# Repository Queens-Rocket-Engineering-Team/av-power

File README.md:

# Avionics Power Delivery (Power Module, Backplane, Screw Switch, etc)
> 2023-2026 Season - Power Delivery Projects

-  Repo contains board's **firmware**, **schematics**, and related **documentation and datasheets**.
-  The **Main** branch contains current functional hardware/software
-  **Branches** contain board revisions/versions or planned features/fixes.
-  If you're contributing, **make sure you're working in a branch other than Main**

### Folder Structure
- [`/Schematics`](./Schematics/) : PCB design files (KiCad V8)  
- [`/Firmware`](./Firmware/) : Arduino C/C++ code (for STM)
- [`/Datasheets`](./Datasheets/) : Datasheets and reference materials

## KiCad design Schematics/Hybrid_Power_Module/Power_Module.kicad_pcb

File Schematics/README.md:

# Schematics

This directory contains all schematics involved in this iteration of the Avionics Power Deliver system.

## Backplane
- Single, large PCB
- Connects all stack "modules" (PCBs)
- Allows communication between modules
- Cleaner routing for power

## Power Module
- Facilitates connections between backplane and external devices
	- Batteries
	- Screw switches

## Screw switches
- Supports manual enabling of power to avionics via screws
- Connected through Power Module

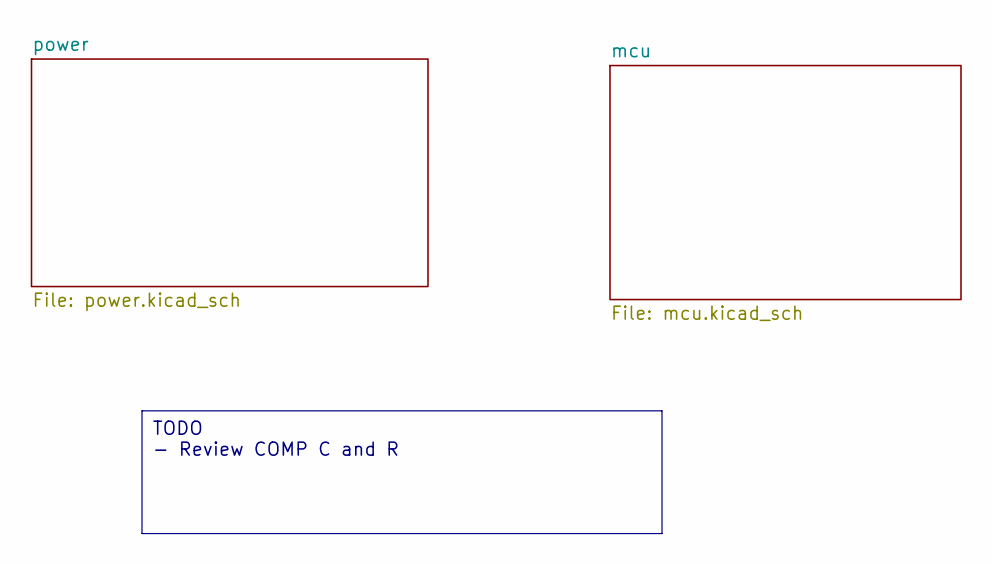
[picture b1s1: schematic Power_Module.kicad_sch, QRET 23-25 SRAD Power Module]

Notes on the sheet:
TODO - Review COMP C and R

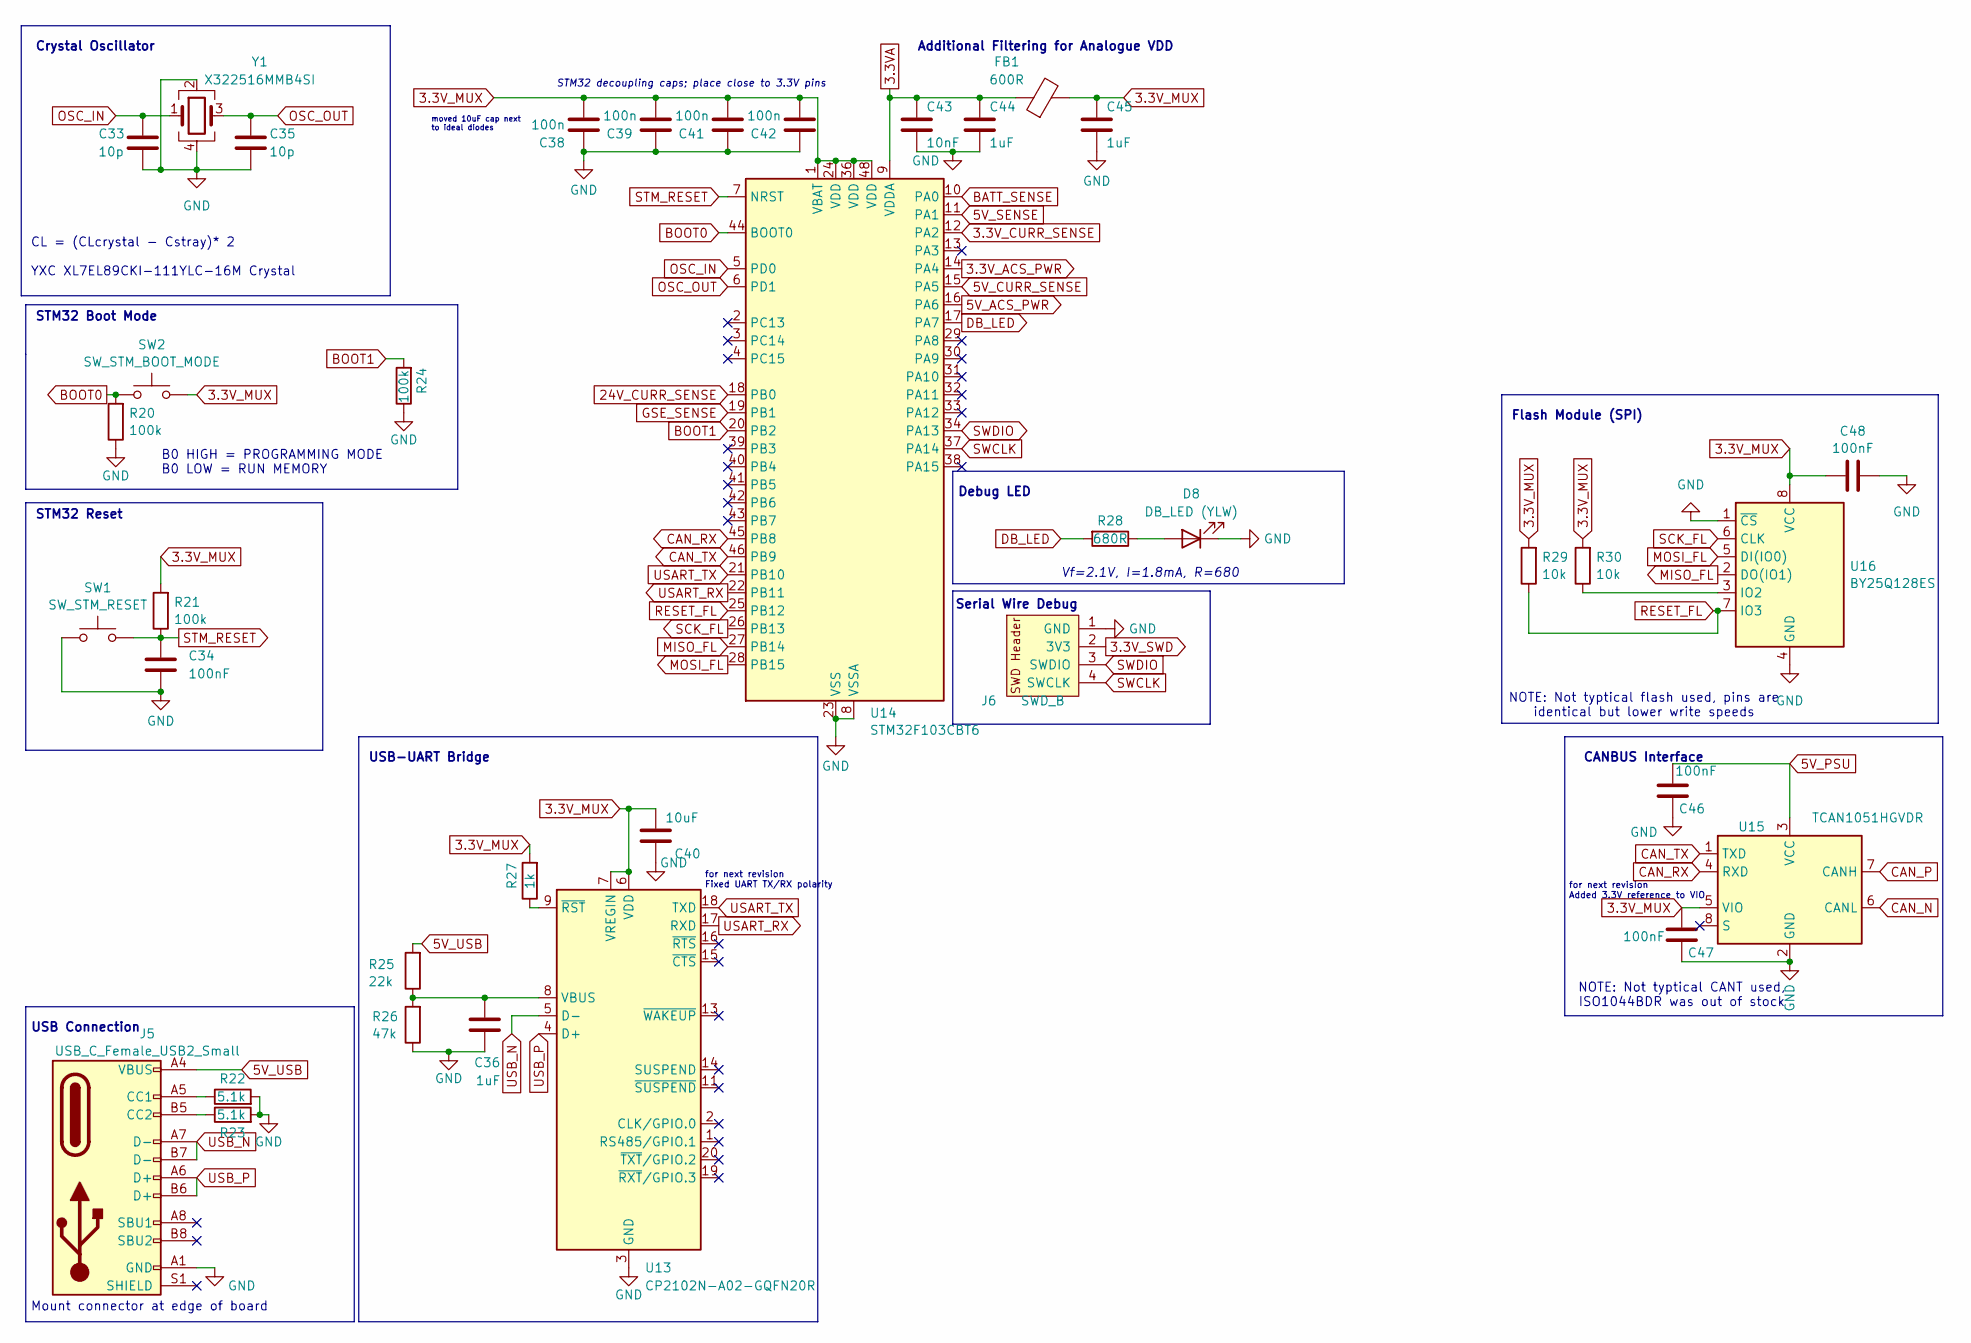
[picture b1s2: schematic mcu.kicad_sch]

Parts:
C33, C35: 10p; C_0402_1005Metric; LCSC C32949
C34, C46, C47, C48: 100nF; C_0603_1608Metric; LCSC C14663
C36, C44, C45: 1uF; C_0603_1608Metric; LCSC C15849
C38, C39, C41, C42: 100n; C_0402_1005Metric; LCSC C1525
C40: 10uF; C_0603_1608Metric; LCSC C96446
C43: 10nF; C_0603_1608Metric; LCSC C57112
D8: DB_LED (YLW); LED_0603_1608Metric; LCSC C2290
FB1: 600R; L_0603_1608Metric; LCSC C1002
J5: USB_C_Female_USB2_Small; USB_C_DB-108PWB; LCSC C5178541
J6: SWD_B; SWD_PinHeader_1x04_P2.54mm_Horizontal_SMD; Digikey 952-3233-ND
R20, R21, R24: 100k; R_0603_1608Metric; LCSC C25803
R22, R23: 5.1k; R_0603_1608Metric; LCSC C23186
R25: 22k; R_0603_1608Metric; LCSC C31850
R26: 47k; R_0603_1608Metric; LCSC C25819
R27: 1k; R_0603_1608Metric; LCSC C21190
R28: 680R; R_0603_1608Metric; LCSC C23228
R29, R30: 10k; R_0603_1608Metric; LCSC C25804
SW1: SW_STM_RESET; SW_Push_1P1T_XKB_TS-1187A; LCSC C318884
SW2: SW_STM_BOOT_MODE; SW_Push_1P1T_XKB_TS-1187A; LCSC C318884
U13: CP2102N-A02-GQFN20R; QFN-20-1EP_3x3mm; LCSC C969913
U14: STM32F103CBT6; LQFP-48_7x7mm_P0.5mm; LCSC C8304
U15: TCAN1051HGVDR; SOIC_1044BDR_TEX; Digikey 296-44225-1-ND
U16: BY25Q128ES; SOIC-8_5.23x5.23mm_P1.27mm; Digikey 5369-BY25Q128ESSIG(R)CT-ND
Y1: X322516MMB4SI; Crystal_SMD_3225-4Pin_3.2x2.5mm; LCSC C13738

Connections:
3.3VA: C43.1, C44.1, FB1.1, U14.9 (VDDA)
3.3V_ACS_PWR: U14.14 (PA4); also elsewhere on the board
3.3V_CURR_SENSE: U14.12 (PA2); also elsewhere on the board
3.3V_MUX: C38.2, C39.2, C40.1, C41.2, C42.2, C45.1, C47.1, C48.1, FB1.2, R21.2, R27.2, R29.2, R30.2, SW2.2, U13.6 (VDD), U13.7 (VREGIN), U14.1 (VBAT), U14.24 (VDD), U14.36 (VDD), U14.48 (VDD), U15.5 (VIO), U16.8 (VCC); also elsewhere on the board
3.3V_SWD: J6.2 (3V3); also elsewhere on the board
5V_ACS_PWR: U14.16 (PA6); also elsewhere on the board
5V_CURR_SENSE: U14.15 (PA5); also elsewhere on the board
5V_PSU: C46.1, U15.3 (VCC); also elsewhere on the board
5V_SENSE: U14.11 (PA1); also elsewhere on the board
5V_USB: J5.A4 (VBUS), J5.A9 (VBUS), J5.B4 (VBUS), J5.B9 (VBUS), R25.2; also elsewhere on the board
24V_CURR_SENSE: U14.18 (PB0); also elsewhere on the board
BATT_SENSE: U14.10 (PA0); also elsewhere on the board
BOOT0: R20.2, SW2.1, U14.44 (BOOT0)
BOOT1: R24.2, U14.20 (PB2)
CAN_N: U15.6 (CANL); also elsewhere on the board
CAN_P: U15.7 (CANH); also elsewhere on the board
CAN_RX: U14.45 (PB8), U15.4 (RXD)
CAN_TX: U14.46 (PB9), U15.1 (TXD)
DB_LED: R28.2, U14.17 (PA7)
GND: C33.2, C34.2, C35.2, C36.1, C38.1, C39.1, C40.2, C41.1, C42.1, C43.2, C44.2, C45.2, C46.2, C47.2, C48.2, D8.1 (K), J5.A1 (GND), J5.A12 (GND), J5.B1 (GND), J5.B12 (GND), J6.1 (GND), R20.1, R22.2, R23.2, R24.1, R26.1, SW1.1, U13.3 (GND), U13.12 (GND), U13.21 (GND), U14.8 (VSSA), U14.23 (VSS), U14.35 (VSS), U14.47 (VSS), U15.2 (GND), U16.1 (~CS), U16.4 (GND), Y1.2, Y1.4; also elsewhere on the board
GSE_SENSE: U14.19 (PB1); also elsewhere on the board
MISO_FL: U14.27 (PB14), U16.2 (DO(IO1))
MOSI_FL: U14.28 (PB15), U16.5 (DI(IO0))
unnamed: D8.2 (A), R28.1
unnamed: J5.A5 (CC1), R22.1
unnamed: J5.B5 (CC2), R23.1
unnamed: C36.2, R25.1, R26.2, U13.8 (VBUS)
unnamed: R27.1, U13.9 (~RST)
unnamed: R30.1, U16.3 (IO2)
OSC_IN: C33.1, U14.5 (PD0), Y1.1
OSC_OUT: C35.1, U14.6 (PD1), Y1.3
RESET_FL: R29.1, U14.25 (PB12), U16.7 (IO3)
SCK_FL: U14.26 (PB13), U16.6 (CLK)
STM_RESET: C34.1, R21.1, SW1.2, U14.7 (NRST)
SWCLK: J6.4 (SWCLK), U14.37 (PA14)
SWDIO: J6.3 (SWDIO), U14.34 (PA13)
USART_RX: U13.17 (RXD), U14.22 (PB11)
USART_TX: U13.18 (TXD), U14.21 (PB10)
USB_N: J5.A7 (D-), J5.B7 (D-), U13.5 (D-)
USB_P: J5.A6 (D+), J5.B6 (D+), U13.4 (D+)

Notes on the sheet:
STM32 Reset
STM32 decoupling caps; place close to 3.3V pins
NOTE: Not typtical CANT used, ISO1044BDR was out of stock
Vf=2.1V, I=1.8mA, R=680
CANBUS Interface
for next revision Fixed UART TX/RX polarity
Flash Module (SPI)
NOTE: Not typtical flash used, pins are identical but lower write speeds
Serial Wire Debug
Debug LED
B0 HIGH = PROGRAMMING MODE B0 LOW = RUN MEMORY
USB-UART Bridge
CL = (CLcrystal - Cstray)* 2 YXC XL7EL89CKI-111YLC-16M Crystal
Mount connector at edge of board
Crystal Oscillator
for next revision Added 3.3V reference to VIO
moved 10uF cap next to ideal diodes
STM32 Boot Mode
USB Connection
Additional Filtering for Analogue VDD

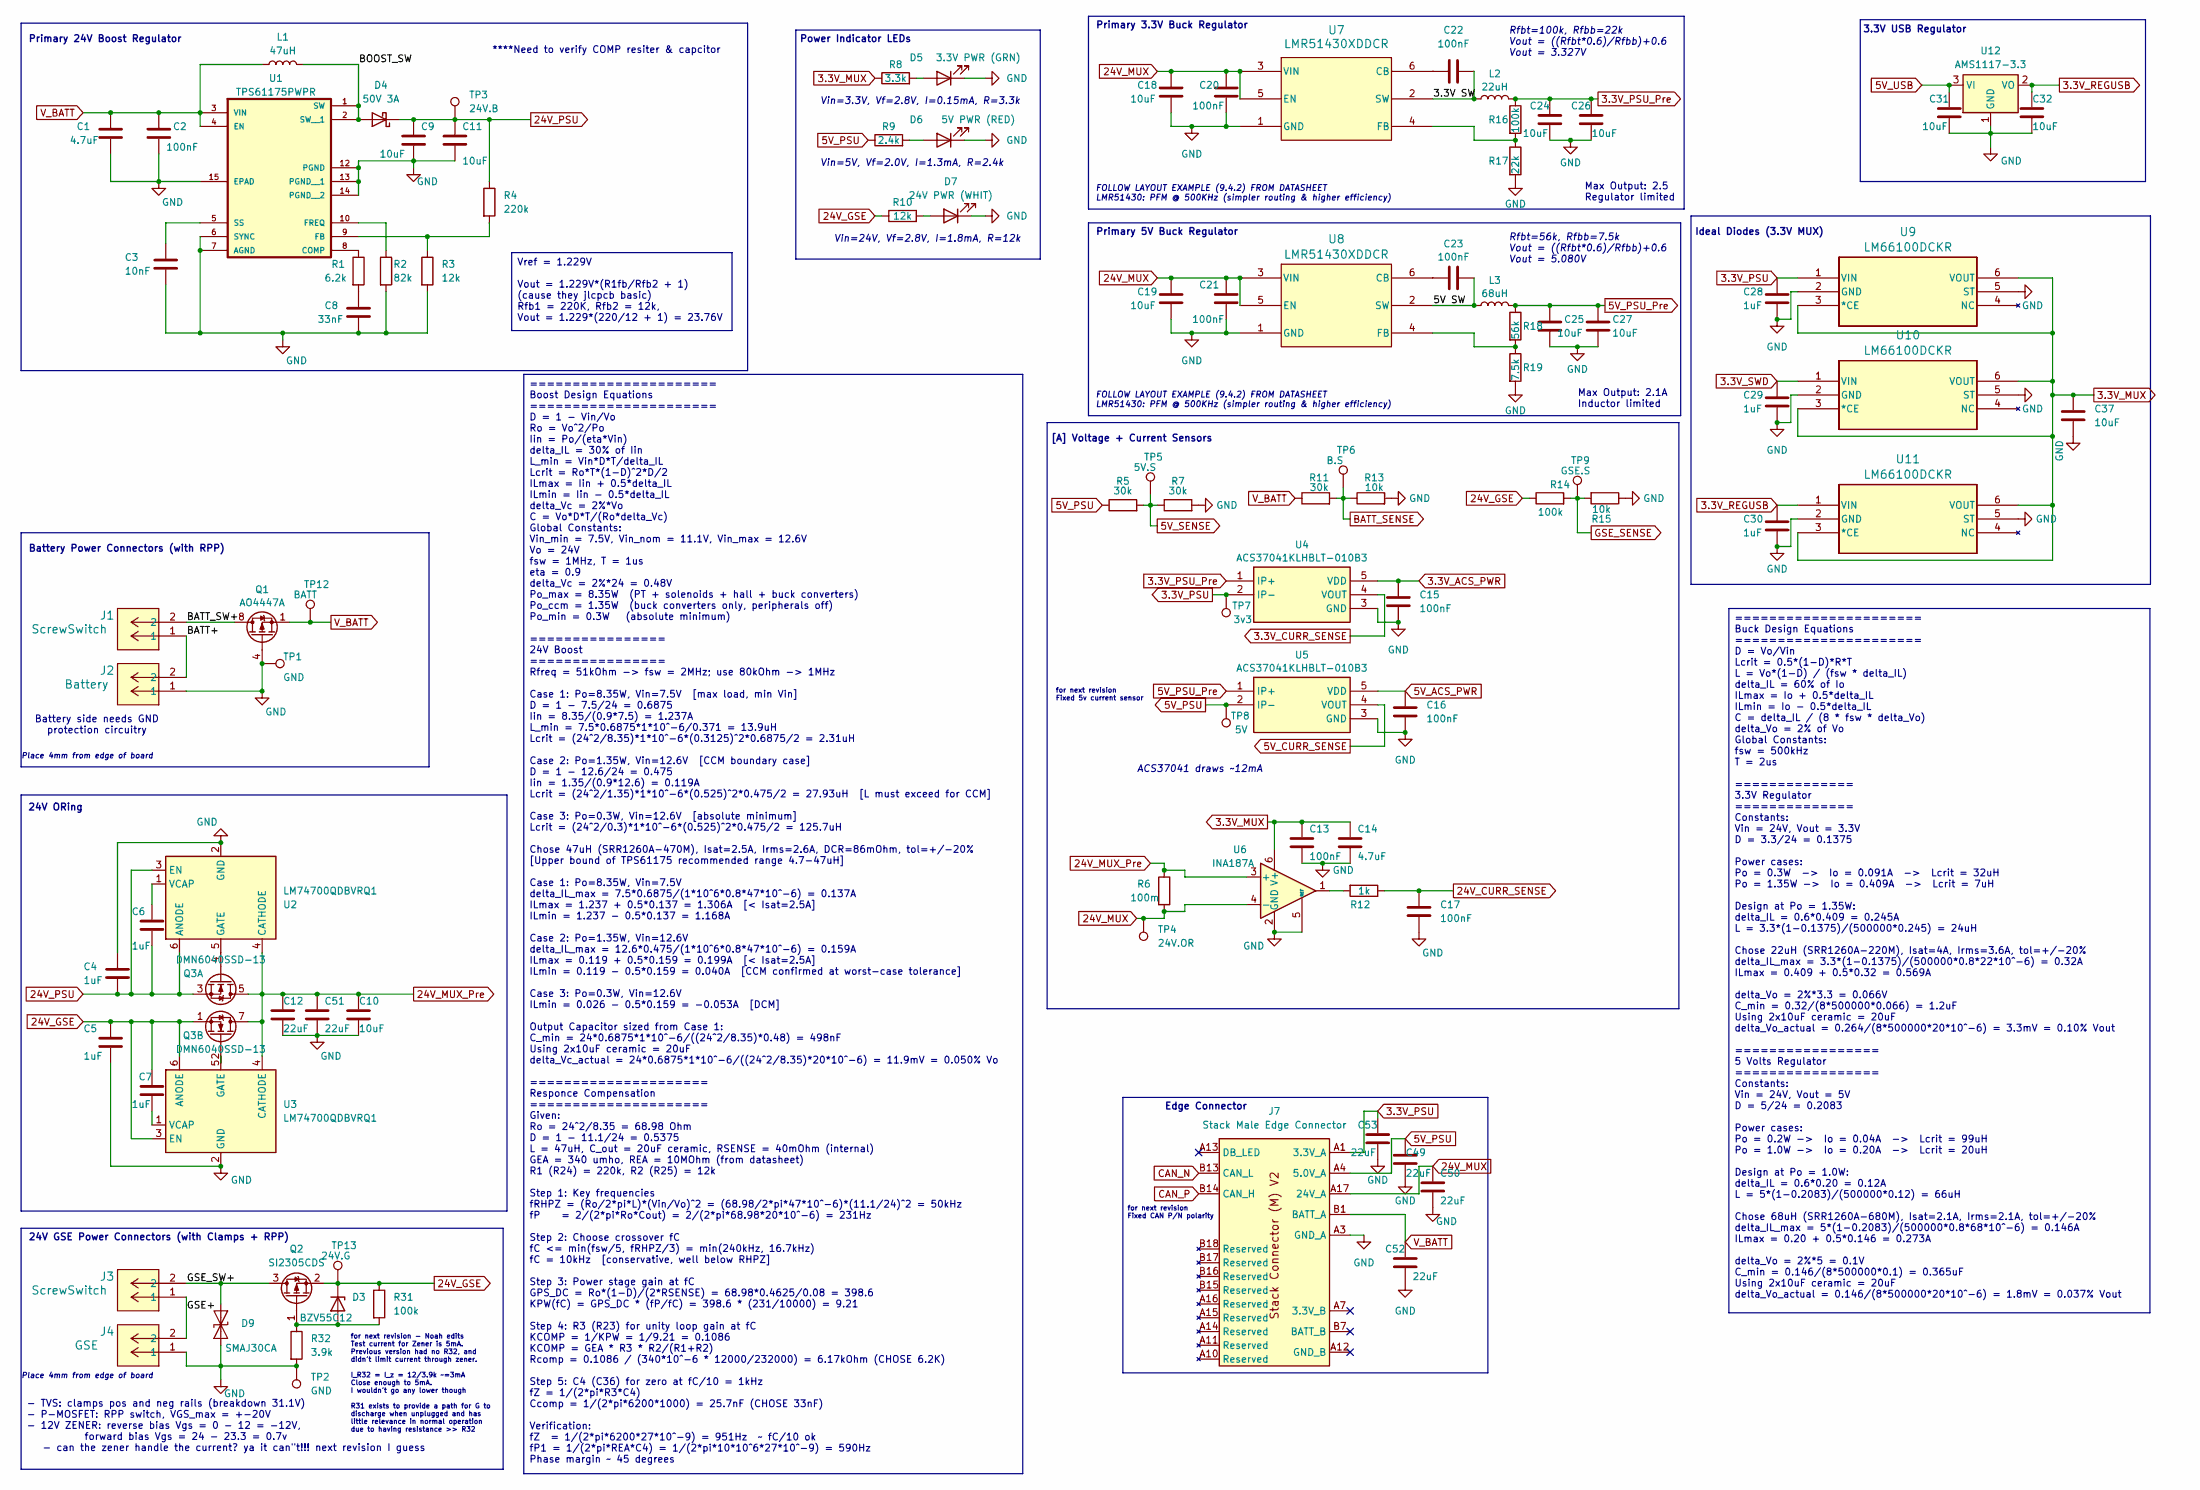
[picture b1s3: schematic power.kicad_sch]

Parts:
C1, C14: 4.7uF; C_0805_2012Metric; LCSC C1779
C2, C13, C15, C16, C17, C20, C21, C22, C23: 100nF; C_0603_1608Metric; LCSC C14663
C3: 10nF; C_0603_1608Metric; LCSC C57112
C4, C5, C6, C7, C28, C29, C30: 1uF; C_0603_1608Metric; LCSC C15849
C8: 33nF; C_0603_1608Metric; LCSC C21117
C9, C10, C11, C18, C19: 10uF; C_1206_3216Metric; LCSC C13585
C12, C50, C51: 22uF; C_1206_3216Metric; Digikey 445-8045-1-ND
C24, C25, C26, C27, C37: 10uF; C_0805_2012Metric; LCSC C15850
C31, C32: 10uF; C_0603_1608Metric; LCSC C96446
C49, C52, C53: 22uF; C_1206_3216Metric; LCSC C12891
D3: BZV55C12; D_MiniMELF; LCSC C545360
D4: 50V 3A; D_SMA; Digikey 112-VSSAF5N50-M3/6BCT-ND
D5: 3.3V PWR (GRN); LED_0805_2012Metric; LCSC C2297
D6: 5V PWR (RED); LED_0805_2012Metric; LCSC C84256
D7: 24V PWR (WHIT); LED_0805_2012Metric; LCSC C34499
D9: SMAJ30CA; D_SMA; LCSC C110043
J1, J3: ScrewSwitch; CONN_2-1445057-2_TYCO; Digikey A33212CT-ND
J2: Battery; CONN_2-1445057-2_TYCO; Digikey A33212CT-ND
J4: GSE; CONN_2-1445057-2_TYCO; Digikey A33212CT-ND
J7: Stack Male Edge Connector; BUS_PCIexpress_x1
L1: 47uH; L_Bourns_SRN8040TA; Digikey 283-SDCHA1V8040-470-RCT-ND
L2: 22uH; L_Bourns_SRN8040TA; Digikey 283-SDCHA1V8040-220-RCT-ND
L3: 68uH; L_Bourns_SRN8040TA; Digikey 283-SDCHA1V8040-680-RCT-ND
Q1: AO4447A; SOIC-8_3.9x4.9mm_P1.27mm; LCSC C125867
Q2: SI2305CDS; SOT-23; LCSC C5182095
Q3: DMN6040SSD-13; SOIC-8_3.9x4.9mm_P1.27mm; LCSC C154876
R1: 6.2k; R_0603_1608Metric; LCSC C4260
R2: 82k; R_0603_1608Metric; LCSC C23254
R3, R10: 12k; R_0603_1608Metric; LCSC C22790
R4: 220k; R_0603_1608Metric; LCSC C22961
R5, R7, R11: 30k; R_0603_1608Metric; LCSC C22984
R6: 100m; R_1206_3216Metric_Pad1.30x1.75mm_HandSolder; Digikey P18940CT-ND
R8: 3.3k; R_0603_1608Metric; LCSC C22978
R9: 2.4k; R_0603_1608Metric; LCSC C22940
R12: 1k; R_0603_1608Metric; LCSC C21190
R13, R15: 10k; R_0603_1608Metric; LCSC C25804
R14, R16: 100k; R_0603_1608Metric; LCSC C25803
R17: 22k; R_0603_1608Metric; LCSC C31850
R18: 56k; R_0603_1608Metric; LCSC C23206
R19: 7.5k; R_0603_1608Metric; LCSC C23234
R31: 100k; R_0603_1608Metric; LCSC C23260
R32: 3.9k; R_0603_1608Metric; LCSC C22809
TP1, TP2: GND; TestPoint_Pad_1.5x1.5mm
TP3: 24V.B; TestPoint_Pad_1.5x1.5mm
TP4: 24V.OR; TestPoint_Pad_1.5x1.5mm
TP5: 5V.S; TestPoint_Pad_1.5x1.5mm
TP6: B.S; TestPoint_Pad_1.5x1.5mm
TP7: 3v3; TestPoint_Pad_1.5x1.5mm
TP8: 5V; TestPoint_Pad_1.5x1.5mm
TP9: GSE.S; TestPoint_Pad_1.5x1.5mm
TP12: BATT; TestPoint_Pad_1.5x1.5mm
TP13: 24V.G; TestPoint_Pad_1.5x1.5mm
U1: TPS61175PWPR; IC_TPS27S100BPWPR; Digikey 296-24013-1-ND
U2, U3: LM74700QDBVRQ1; SOT-23-6; LCSC C2941042
U4, U5: ACS37041KLHBLT-010B3; APS12628LLHALTBAP_HandSolder; Digikey 620-ACS37041KLHBLT-010B3CT-ND
U6: INA187A; SOT-23-6; Digikey 296-INA187A1IDBVRCT-ND
U7, U8: LMR51430XDDCR; SOT-23-6_Handsoldering; Digikey 296-LMR51430XDDCRCT-ND
U9, U10, U11: LM66100DCKR; SC-70-6; LCSC C2869734
U12: AMS1117-3.3; SOT-223-3_TabPin2; LCSC C6186

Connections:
3.3V_ACS_PWR: C15.1, U4.5 (VDD); also elsewhere on the board
3.3V_CURR_SENSE: U4.4 (VOUT); also elsewhere on the board
3.3V_MUX: C13.1, C14.1, C37.1, R8.1, U6.6 (V+), U9.3 (*CE), U9.6 (VOUT), U10.3 (*CE), U10.6 (VOUT), U11.3 (*CE), U11.6 (VOUT); also elsewhere on the board
3.3V_PSU: C28.1, C53.1, J7.A1 (3.3V_A), J7.A2 (3.3V_A), TP7.1 (1_1), U4.2 (IP-), U9.1 (VIN)
3.3V_PSU_Pre: C24.1, C26.1, L2.1, R16.1, U4.1 (IP+)
3.3V_REGUSB: C30.1, C32.1, U11.1 (VIN), U12.2 (VO)
3.3V_SWD: C29.1, U10.1 (VIN); also elsewhere on the board
5V_ACS_PWR: C16.1, U5.5 (VDD); also elsewhere on the board
5V_CURR_SENSE: U5.4 (VOUT); also elsewhere on the board
5V_PSU: C49.1, J7.A4 (5.0V_A), J7.A5 (5.0V_A), R5.1, R9.1, TP8.1 (1_1), U5.2 (IP-); also elsewhere on the board
5V_PSU_Pre: C25.1, C27.1, L3.2, R18.1, U5.1 (IP+)
5V_SENSE: R5.2, R7.1, TP5.1 (1_1); also elsewhere on the board
5V_USB: C31.1, U12.3 (VI); also elsewhere on the board
24V_CURR_SENSE: C17.1, R12.1; also elsewhere on the board
24V_GSE: C5.1, C7.1, D3.1 (K), Q2.2 (S), Q3.1 (S1), R10.1, R14.1, R31.1, TP13.1 (1_1), U3.3 (EN), U3.6 (ANODE)
24V_MUX: C18.1, C19.1, C20.1, C21.1, C50.1, J7.A17 (24V_A), J7.A18 (24V_A), R6.2, TP4.1 (1_1), U6.4 (-), U7.3 (VIN), U7.5 (EN), U8.3 (VIN), U8.5 (EN)
24V_MUX_Pre: C10.1, C12.1, C51.1, Q3.5 (D2), Q3.6 (D2), Q3.7 (D1), Q3.8 (D1), R6.1, U2.4 (CATHODE), U3.4 (CATHODE), U6.3 (+)
24V_PSU: C4.2, C6.2, C9.1, C11.1, D4.1 (K), Q3.3 (S2), R4.1, TP3.1 (1_1), U2.3 (EN), U2.6 (ANODE)
/power/3.3V SW: C22.2, L2.2, U7.2 (SW)
/power/5V SW: C23.1, L3.1, U8.2 (SW)
/power/BATT+: J1.1, J2.2
/power/BATT_SW+: J1.2, Q1.5 (D), Q1.6 (D), Q1.7 (D), Q1.8 (D)
/power/BOOST_SW: D4.2 (A), L1.2, U1.1 (SW), U1.2 (SW__1)
/power/GSE+: J3.1, J4.2
/power/GSE_SW+: D9.2 (A2), J3.2, Q2.3 (D)
BATT_SENSE: R11.2, R13.1, TP6.1 (1_1); also elsewhere on the board
CAN_N: J7.B13 (CAN_L); also elsewhere on the board
CAN_P: J7.B14 (CAN_H); also elsewhere on the board
GND: C1.2, C2.2, C3.2, C4.1, C5.2, C8.2, C9.2, C10.2, C11.2, C12.2, C13.2, C14.2, C15.2, C16.2, C17.2, C18.2, C19.2, C20.2, C21.2, C24.2, C25.2, C26.2, C27.2, C28.2, C29.2, C30.2, C31.2, C32.2, C37.2, C49.2, C50.2, C51.2, C52.2, C53.2, D5.1 (K), D6.1 (K), D7.1 (K), D9.1 (A1), J2.1, J4.1, J7.A3 (GND_A), J7.A6 (GND_A), J7.B4 (GND_A), J7.B5 (GND_A), J7.B6 (GND_A), Q1.4 (G), R2.2, R3.2, R7.2, R13.2, R15.1, R17.2, R19.2, R32.2, TP1.1 (1_1), TP2.1 (1_1), U1.6 (SYNC), U1.7 (AGND), U1.12 (PGND), U1.13 (PGND__1), U1.14 (PGND__2), U1.15 (EPAD), U2.2 (GND), U3.2 (GND), U4.3 (GND), U5.3 (GND), U6.2 (GND), U6.5 (REF), U7.1 (GND), U8.1 (GND), U9.2 (GND), U9.5 (ST), U10.2 (GND), U10.5 (ST), U11.2 (GND), U11.5 (ST), U12.1 (GND); also elsewhere on the board
GSE_SENSE: R14.2, R15.2, TP9.1 (1_1); also elsewhere on the board
unnamed: C8.1, R1.2
unnamed: D3.2 (A), Q2.1 (G), R31.2, R32.1
unnamed: D5.2 (A), R8.2
unnamed: D6.2 (A), R9.2
unnamed: D7.2 (A), R10.2
unnamed: Q3.2 (G1), U3.5 (GATE)
unnamed: Q3.4 (G2), U2.5 (GATE)
unnamed: R12.2, U6.1
unnamed: R1.1, U1.8 (COMP)
unnamed: R3.1, R4.2, U1.9 (FB)
unnamed: R2.1, U1.10 (FREQ)
unnamed: C3.1, U1.5 (SS)
unnamed: C6.1, U2.1 (VCAP)
unnamed: C7.2, U3.1 (VCAP)
unnamed: C22.1, U7.6 (CB)
unnamed: R16.2, R17.1, U7.4 (FB)
unnamed: C23.2, U8.6 (CB)
unnamed: R18.2, R19.1, U8.4 (FB)
V_BATT: C1.1, C2.1, C52.1, J7.B1 (BATT_A), J7.B2 (BATT_A), J7.B3 (BATT_A), L1.1, Q1.1 (S), Q1.2 (S), Q1.3 (S), R11.1, TP12.1 (1_1), U1.3 (VIN), U1.4 (EN)

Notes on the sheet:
for next revision Fixed CAN P/N polarity
Vin=3.3V, Vf=2.8V, I=0.15mA, R=3.3k
for next revision Fixed 5v current sensor
Power Indicator LEDs
24V GSE Power Connectors (with Clamps + RPP)
[A] Voltage + Current Sensors
ACS37041 draws ~12mA
FOLLOW LAYOUT EXAMPLE (9.4.2) FROM DATASHEET LMR51430: PFM @ 500KHz (simpler routing & higher efficiency)
Ideal Diodes (3.3V MUX)
Primary 24V Boost Regulator
****Need to verify COMP resiter & capcitor
3.3V USB Regulator
Max Output: 2.5 Regulator limited
for next revision - Noah edits Test current for Zener is 5mA. Previous version had no R32, and didn't limit current through zener. I_R32 = I_z = 12/3.9k ~=3mA Close enough to 5mA. I wouldn't go any lower though R31 exists to provide a path for G to discharge when unplugged and has little relevance 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
Battery Power Connectors (with RPP)
Place 4mm from edge of board
Max Output: 2.1A Inductor limited
Primary 3.3V Buck Regulator
Rfbt=100k, Rfbb=22k Vout = ((Rfbt*0.6)/Rfbb)+0.6 Vout = 3.327V
Rfbt=56k, Rfbb=7.5k Vout = ((Rfbt*0.6)/Rfbb)+0.6 Vout = 5.080V
24V ORing
Vin=5V, Vf=2.0V, I=1.3mA, R=2.4k
Battery side needs GND protection circuitry
- TVS: clamps pos and neg rails (breakdown 31.1V) - P-MOSFET: RPP switch, VGS_max = +-20V - 12V ZENER: reverse bias Vgs = 0 - 12 = -12V, forward bias Vgs = 24 - 23.3 = 0.7v - can the zener handle the current? ya it can"t!!! next revision I guess
Vin=24V, Vf=2.8V, I=1.8mA, R=12k
Edge Connector
Primary 5V Buck Regulator
Vref = 1.229V Vout = 1.229V*(R1fb/Rfb2 + 1) (cause they jlcpcb basic) Rfb1 = 220K, Rfb2 = 12k, Vout = 1.229*(220/12 + 1) = 23.76V
====================== Boost Design Equations ====================== D = 1 - Vin/Vo Ro = Vo^2/Po Iin = Po/(eta*Vin) delta_IL = 30% of Iin L_min = Vin*D*T/delta_IL Lcrit = Ro*T*(1-D)^2*D/2 ILmax = Iin + 0.5*delta_IL ILmin = Iin - 0.5*delta_IL delta_Vc = 2%*Vo C = Vo*D*T/(Ro*delta_Vc) Global Constant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
====================== Buck Design Equations ====================== D = Vo/Vin Lcrit = 0.5*(1-D)*R*T L = Vo*(1-D) / (fsw * delta_IL) delta_IL = 60% of Io ILmax = Io + 0.5*delta_IL ILmin = Io - 0.5*delta_IL C = delta_IL / (8 * fsw * delta_Vo) delta_Vo = 2% of Vo Global Constants: fsw = 500kHz T = 2u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

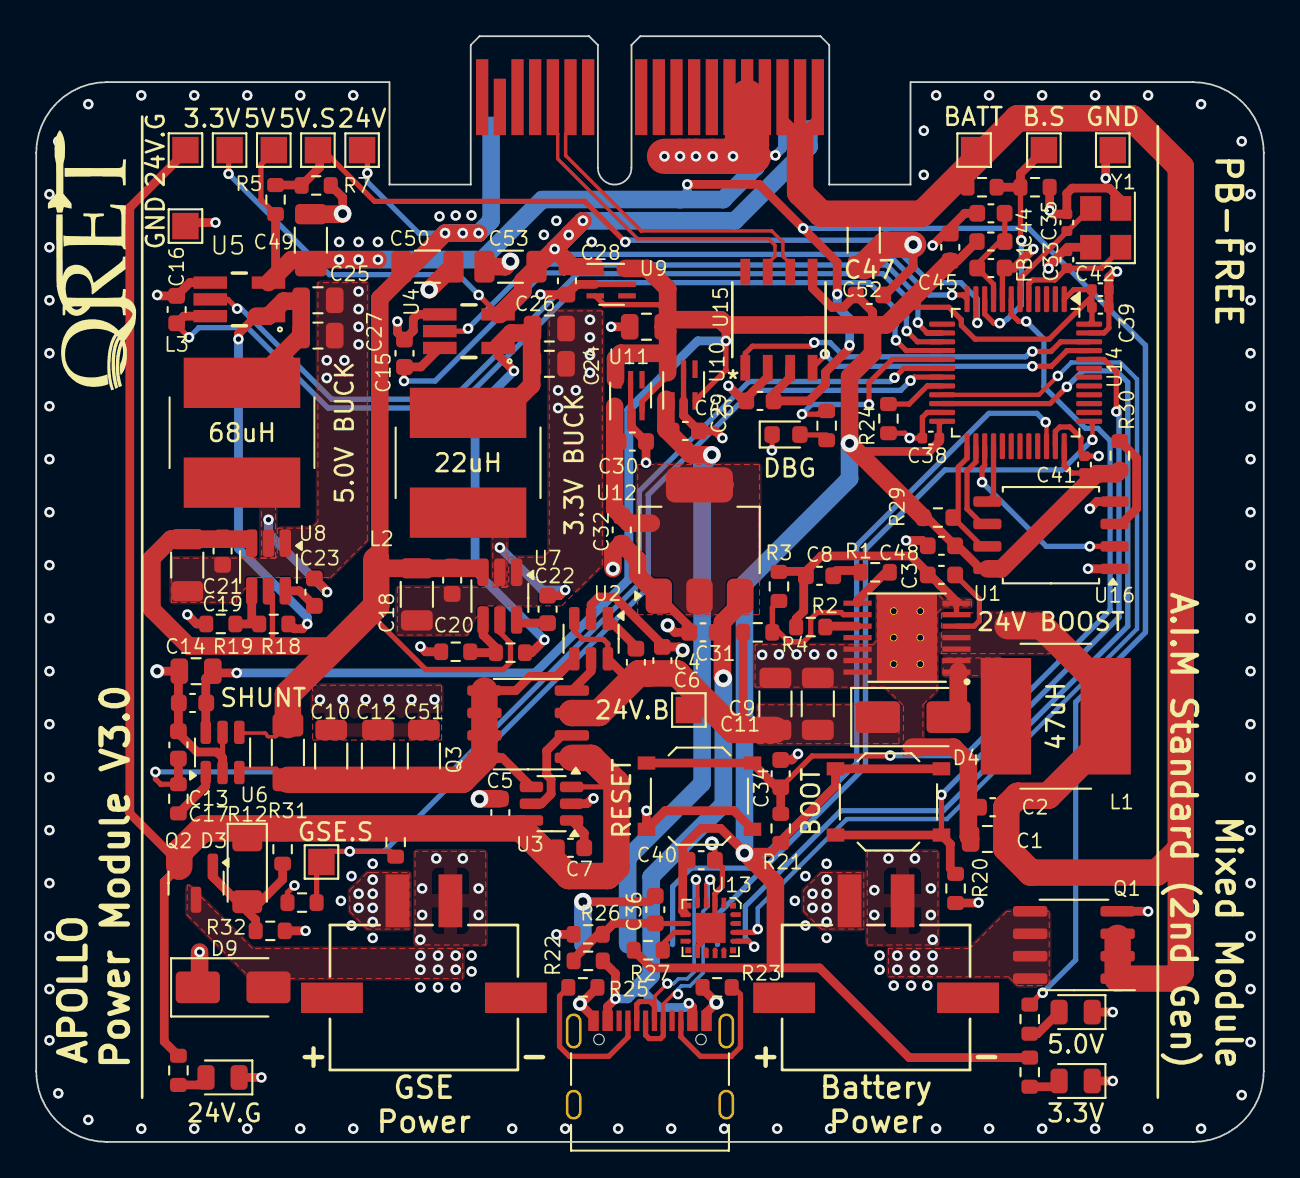
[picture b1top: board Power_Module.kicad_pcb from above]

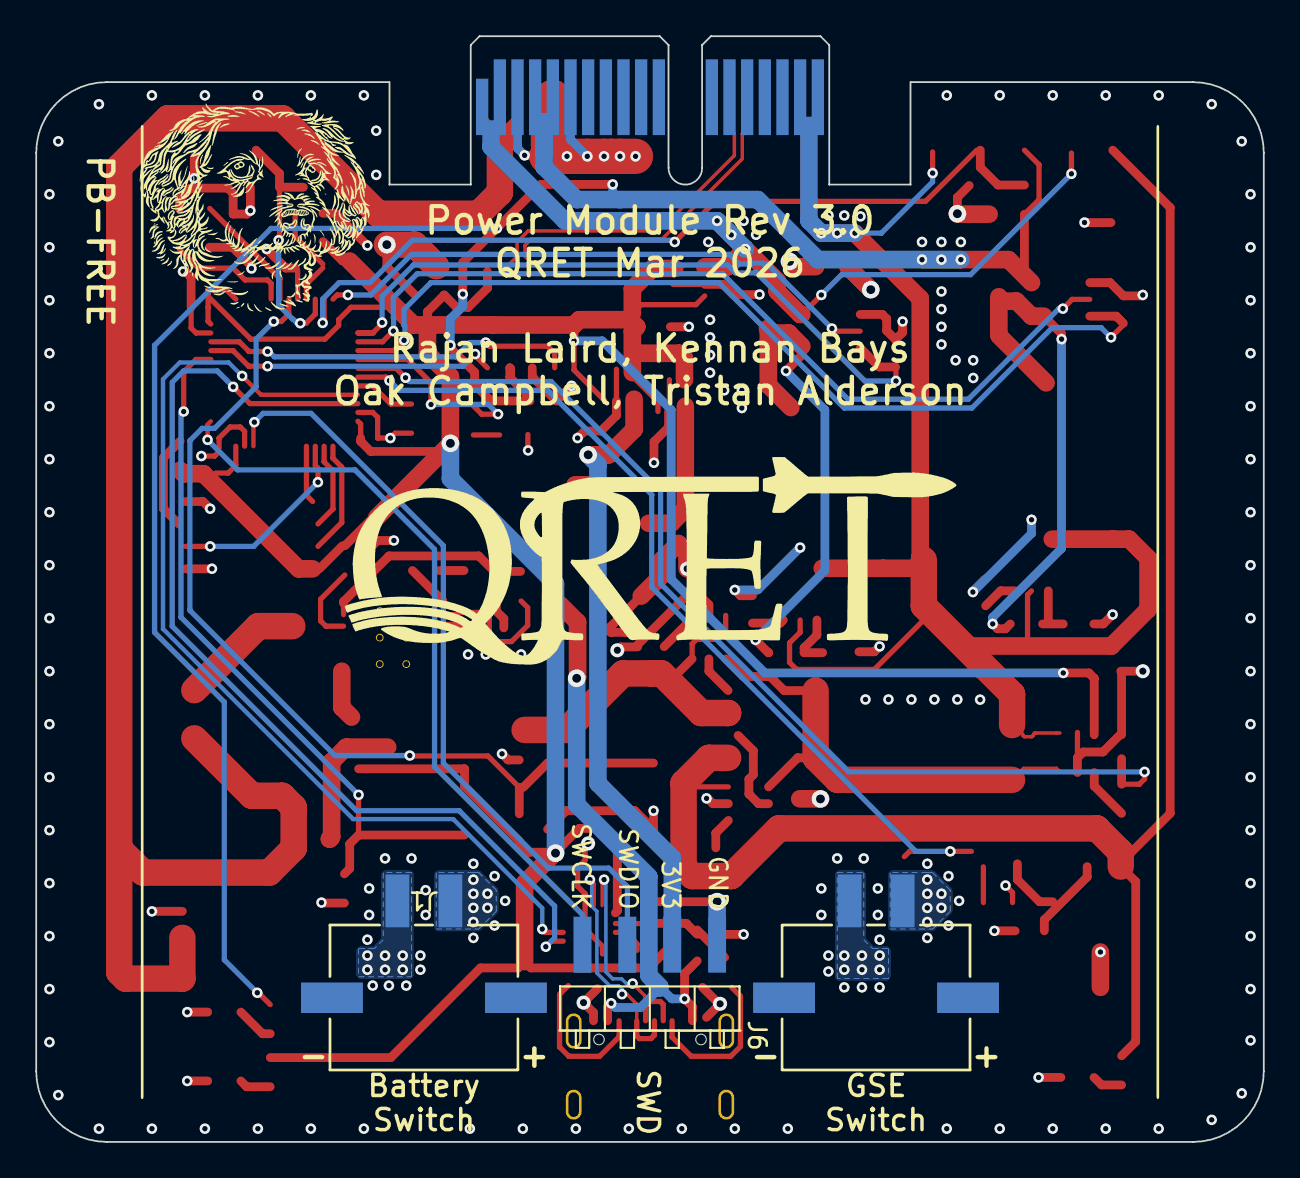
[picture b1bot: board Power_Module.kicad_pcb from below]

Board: 4 copper layers, 69.5 x 62.6 mm, 136 parts (3 on the bottom side), 74 nets.

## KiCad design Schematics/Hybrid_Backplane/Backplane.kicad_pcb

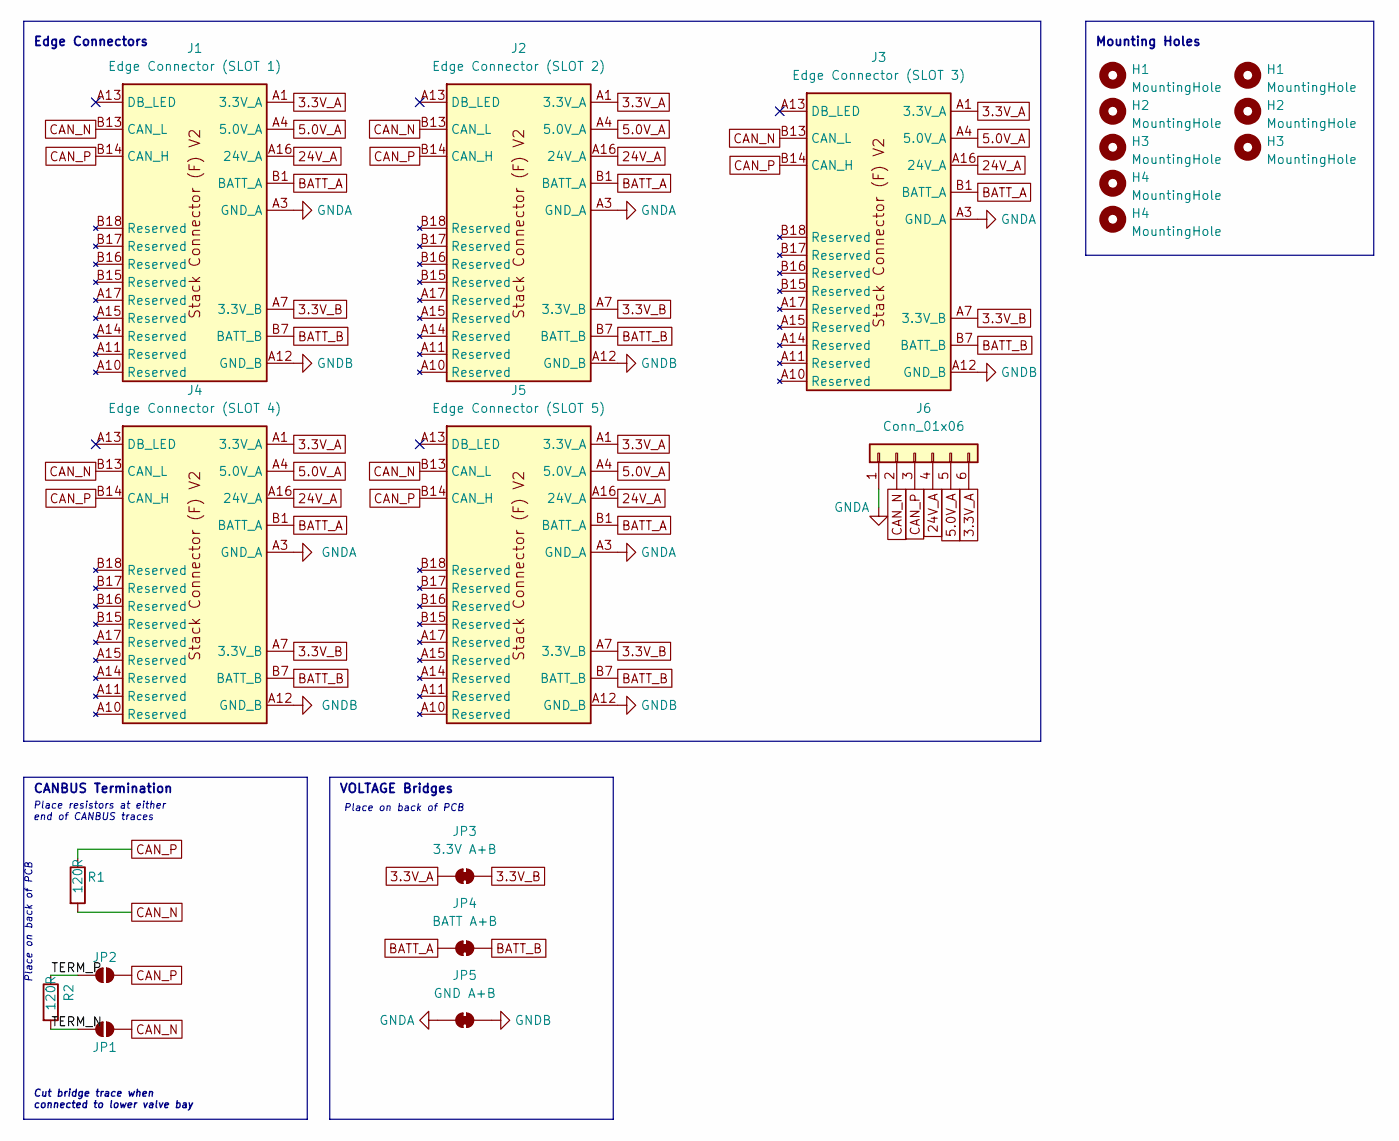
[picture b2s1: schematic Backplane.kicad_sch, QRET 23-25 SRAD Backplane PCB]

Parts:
H1, H2, H3, H4: MountingHole; MountingHole_3.2mm_M3_ISO14580_Pad
J1: Edge Connector (SLOT 1); AMPHENOL_10018784-10210TLF
J2: Edge Connector (SLOT 2); AMPHENOL_10018784-10210TLF
J3: Edge Connector (SLOT 3); AMPHENOL_10018784-10210TLF
J4: Edge Connector (SLOT 4); AMPHENOL_10018784-10210TLF
J5: Edge Connector (SLOT 5); AMPHENOL_10018784-10210TLF
J6: Conn_01x06; CONN_SD-105314-100_06_MOL; Digikey WM1821-ND
JP1: N JMP; SolderJumper-2_P1.3mm_Open_RoundedPad1.0x1.5mm
JP2: P JMP; SolderJumper-2_P1.3mm_Open_RoundedPad1.0x1.5mm
JP3: 3.3V A+B; SolderJumper-2_P1.3mm_Bridged2Bar_RoundedPad1.0x1.5mm
JP4: BATT A+B; SolderJumper-2_P1.3mm_Bridged2Bar_RoundedPad1.0x1.5mm
JP5: GND A+B; SolderJumper-2_P1.3mm_Bridged2Bar_RoundedPad1.0x1.5mm
R1, R2: 120R; R_0805_2012Metric_Pad1.20x1.40mm_HandSolder; Digikey A129738CT-ND

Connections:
3.3V_A: J1.A1 (3.3V_A), J1.A2 (3.3V_A), J2.A1 (3.3V_A), J2.A2 (3.3V_A), J3.A1 (3.3V_A), J3.A2 (3.3V_A), J4.A1 (3.3V_A), J4.A2 (3.3V_A), J5.A1 (3.3V_A), J5.A2 (3.3V_A), J6.6, JP3.1 (A)
3.3V_B: J1.A7 (3.3V_B), J1.A8 (3.3V_B), J2.A7 (3.3V_B), J2.A8 (3.3V_B), J3.A7 (3.3V_B), J3.A8 (3.3V_B), J4.A7 (3.3V_B), J4.A8 (3.3V_B), J5.A7 (3.3V_B), J5.A8 (3.3V_B), JP3.2 (B)
5.0V_A: J1.A4 (5.0V_A), J1.A5 (5.0V_A), J2.A4 (5.0V_A), J2.A5 (5.0V_A), J3.A4 (5.0V_A), J3.A5 (5.0V_A), J4.A4 (5.0V_A), J4.A5 (5.0V_A), J5.A4 (5.0V_A), J5.A5 (5.0V_A), J6.5
24V_A: J1.A16 (24V_A), J1.A18 (24V_A), J2.A16 (24V_A), J2.A18 (24V_A), J3.A16 (24V_A), J3.A18 (24V_A), J4.A16 (24V_A), J4.A18 (24V_A), J5.A16 (24V_A), J5.A18 (24V_A), J6.4
/TERM_N: JP1.2 (B), R2.2
/TERM_P: JP2.2 (B), R2.1
BATT_A: J1.B1 (BATT_A), J1.B2 (BATT_A), J1.B3 (BATT_A), J2.B1 (BATT_A), J2.B2 (BATT_A), J2.B3 (BATT_A), J3.B1 (BATT_A), J3.B2 (BATT_A), J3.B3 (BATT_A), J4.B1 (BATT_A), J4.B2 (BATT_A), J4.B3 (BATT_A), J5.B1 (BATT_A), J5.B2 (BATT_A), J5.B3 (BATT_A), JP4.1 (A)
BATT_B: J1.B7 (BATT_B), J1.B8 (BATT_B), J1.B9 (BATT_B), J2.B7 (BATT_B), J2.B8 (BATT_B), J2.B9 (BATT_B), J3.B7 (BATT_B), J3.B8 (BATT_B), J3.B9 (BATT_B), J4.B7 (BATT_B), J4.B8 (BATT_B), J4.B9 (BATT_B), J5.B7 (BATT_B), J5.B8 (BATT_B), J5.B9 (BATT_B), JP4.2 (B)
CAN_N: J1.B13 (CAN_L), J2.B13 (CAN_L), J3.B13 (CAN_L), J4.B13 (CAN_L), J5.B13 (CAN_L), J6.2, JP1.1 (A), R1.2
CAN_P: J1.B14 (CAN_H), J2.B14 (CAN_H), J3.B14 (CAN_H), J4.B14 (CAN_H), J5.B14 (CAN_H), J6.3, JP2.1 (A), R1.1
GNDA: J1.A3 (GND_A), J1.A6 (GND_A), J1.B4 (GND_A), J1.B5 (GND_A), J1.B6 (GND_A), J2.A3 (GND_A), J2.A6 (GND_A), J2.B4 (GND_A), J2.B5 (GND_A), J2.B6 (GND_A), J3.A3 (GND_A), J3.A6 (GND_A), J3.B4 (GND_A), J3.B5 (GND_A), J3.B6 (GND_A), J4.A3 (GND_A), J4.A6 (GND_A), J4.B4 (GND_A), J4.B5 (GND_A), J4.B6 (GND_A), J5.A3 (GND_A), J5.A6 (GND_A), J5.B4 (GND_A), J5.B5 (GND_A), J5.B6 (GND_A), J6.1, JP5.1 (A)
GNDB: J1.A9 (GND_B), J1.A12 (GND_B), J1.B10 (GND_B), J1.B11 (GND_B), J1.B12 (GND_B), J2.A9 (GND_B), J2.A12 (GND_B), J2.B10 (GND_B), J2.B11 (GND_B), J2.B12 (GND_B), J3.A9 (GND_B), J3.A12 (GND_B), J3.B10 (GND_B), J3.B11 (GND_B), J3.B12 (GND_B), J4.A9 (GND_B), J4.A12 (GND_B), J4.B10 (GND_B), J4.B11 (GND_B), J4.B12 (GND_B), J5.A9 (GND_B), J5.A12 (GND_B), J5.B10 (GND_B), J5.B11 (GND_B), J5.B12 (GND_B), JP5.2 (B)

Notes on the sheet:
Cut bridge trace when connected to lower valve bay
CANBUS Termination
Place on back of PCB
Place resistors at either end of CANBUS traces
VOLTAGE Bridges
Mounting Holes
Edge Connectors
